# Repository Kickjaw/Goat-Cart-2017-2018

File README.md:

# Goat-Cart-2017-2018
Repository for all code, circuit diagrams, datasheets, and other useful documents.

stuff

jared was here

jade did stuff to sabertooth

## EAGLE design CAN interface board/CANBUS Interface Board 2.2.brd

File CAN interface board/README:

VERSION2 from 2017-18 MQP Team, as of March 2018 this is the CAN board.

Read more at the 2017-18 MQP report section 3.1

The second version of the board fixed the errors found in the first PCB and further optimized the layout.
The CAN transceiver was replaced with a SN65HVD23x 3.3-V CAN Bus Transceiver. [16]

The second board has:
•	Voltage regulation
•	+12V to +5V 
•	+5V to +3V3 (Teensy)
•	2 Power LEDs
•	+5V 
•	+3V3 
•	3 Programmable LEDs
•	2 differential CAN ports (link together via daisy chain method)
•	2 SPI Ports
•	2 Serial Ports
•	2 I2C Ports
•	16 Digital Pins
•	10 Analog Pins
•	5 PWM Pins

The primary goal of this design was to have many different methods of communication from the Teensy so that it could communicate to any type of sensor that a future team might use on the Goat Cart. Another reason for having numerous pins available was to allow a single Teensy to be used to control multiple subsystems. The only problem with the design was that, since the pins are software programmable, using a pin for a certain function could limit the availability of its other functions. An example of this is using pin 10 for PWM prevents its use as one of the SPI channels. The list of connector pinouts can be seen in Table 4. Figures 13 show the circuit and PCB of the second version of the CAN interface board.

Table 5: Pinouts of the Teensy used in the CAN Interface Board
Pinouts for the CAN Interface Board
1.	GND 
2.	3.3V
3.	CAN L0
4.	CAN H0
5.	CAN L
6.	CAN H
7.	Pin 32 - D/A/RX4/CS1
8.	Pin 31 -  D/A/TX4/SCK1
9.	Pin 12 - D/MISO0
10.	Pin 11 -  D/MISI0
11.	Pin 10 - D/PWM/TX2/CS0
12.	Pin 13 - D/SCK0	13.	Pin 33 - D/A/TX5
14.	Pin 34 - D/A/RX5
15.	Pin 37 - D/A/PWM/SCL1
16.	Pin 38 - D/A/PWM/SDA1
17.	Pin 18 - D/A/SDA0
18.	Pin 19 - D/A/SCL0
19.	Pin 22 - D/A/PWM
20.	Pin 23 - D/A/PWM
21.	Pin 1 -  D/TX1/MISO1
22.	Pin 0 - D/RX1/MOSI1
23.	3.3V
24.	GND

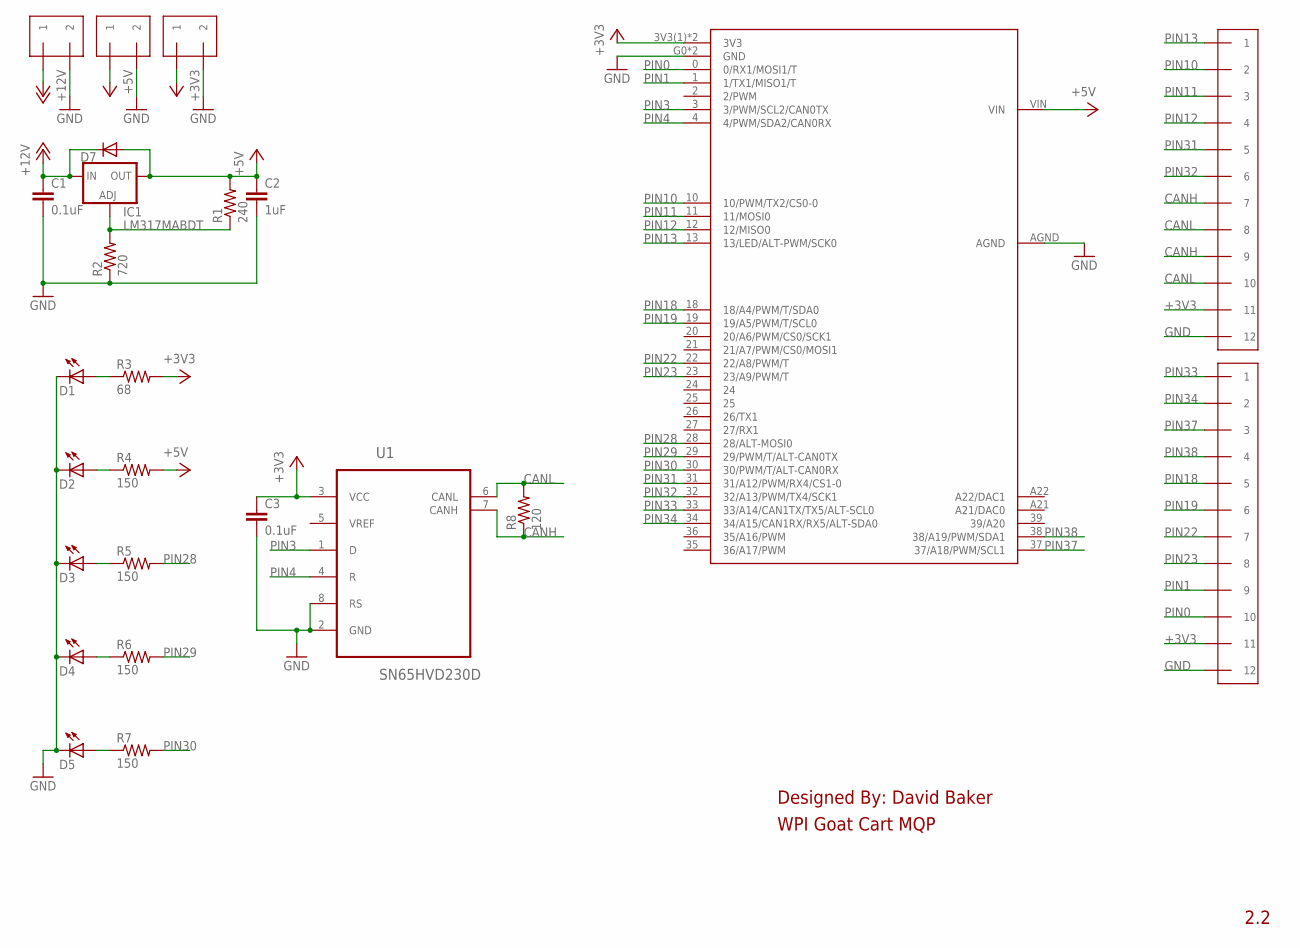
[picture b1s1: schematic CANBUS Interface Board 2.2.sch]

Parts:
C1, C3: 0.1uF; C0603
C2: 1uF; C0603
D1, D2, D3, D4, D5: LEDSML0603; SML0603
D7: DIODE-DO-214AC; DO-214AC
IC1: LM317MABDT; DPACK
J1, J2: 1984617X12; 12POSTERMBLOCK
J3, J4, J5: 1984617; 2POSTERMBLOCK
R1: 240; R0603
R2: 720; R0603
R3: 68; R0603
R4, R5, R6, R7: 150; R0603
R8: 120; R0603
U1: SN65HVD230D; SOIC127P600X175-8N
U2: TEENSY3_6--ALLPINS; T36

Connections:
+3V3: C3.1, J1.11, J2.11, J5.1, R3.2, U1.3 (VCC), U2.3V3(1) (3V3), U2.3V3(3) (3V3)
+5V: C2.1, D7.A, IC1.4 (OUT), J4.1, R1.2, R4.2, U2.VIN
+12V: C1.1, D7.C, IC1.3 (IN), J3.1
CANH: J1.7, J1.9, R8.1, U1.7 (CANH)
CANL: J1.8, J1.10, R8.2, U1.6 (CANL)
GND: C1.2, C2.2, C3.2, D1.C, D2.C, D3.C, D4.C, D5.C, J1.12, J2.12, J3.2, J4.2, J5.2, R2.1, U1.2 (GND), U1.8 (RS), U2.AGND, U2.G0 (GND), U2.G2 (GND)
unnamed: IC1.1 (ADJ), R1.1, R2.2
unnamed: D1.A, R3.1
unnamed: D2.A, R4.1
unnamed: D3.A, R5.1
unnamed: D4.A, R6.1
unnamed: D5.A, R7.1
PIN0: J2.10, U2.0 (0/RX1/MOSI1/T)
PIN1: J2.9, U2.1 (1/TX1/MISO1/T)
PIN3: U1.1 (D), U2.3 (3/PWM/SCL2/CAN0TX)
PIN4: U1.4 (R), U2.4 (4/PWM/SDA2/CAN0RX)
PIN10: J1.2, U2.10 (10/PWM/TX2/CS0-0)
PIN11: J1.3, U2.11 (11/MOSI0)
PIN12: J1.4, U2.12 (12/MISO0)
PIN13: J1.1, U2.13 (13/LED/ALT-PWM/SCK0)
PIN18: J2.5, U2.18 (18/A4/PWM/T/SDA0)
PIN19: J2.6, U2.19 (19/A5/PWM/T/SCL0)
PIN22: J2.7, U2.22 (22/A8/PWM/T)
PIN23: J2.8, U2.23 (23/A9/PWM/T)
PIN28: R5.2, U2.28 (28/ALT-MOSI0)
PIN29: R6.2, U2.29 (29/PWM/T/ALT-CAN0TX)
PIN30: R7.2, U2.30 (30/PWM/T/ALT-CAN0RX)
PIN31: J1.5, U2.31 (31/A12/PWM/RX4/CS1-0)
PIN32: J1.6, U2.32 (32/A13/PWM/TX4/SCK1)
PIN33: J2.1, U2.33 (33/A14/CAN1TX/TX5/ALT-SCL0)
PIN34: J2.2, U2.34 (34/A15/CAN1RX/RX5/ALT-SDA0)
PIN37: J2.3, U2.37 (37/A18/PWM/SCL1)
PIN38: J2.4, U2.38 (38/A19/PWM/SDA1)

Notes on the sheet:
Designed By: David Baker
WPI Goat Cart MQP
2.2

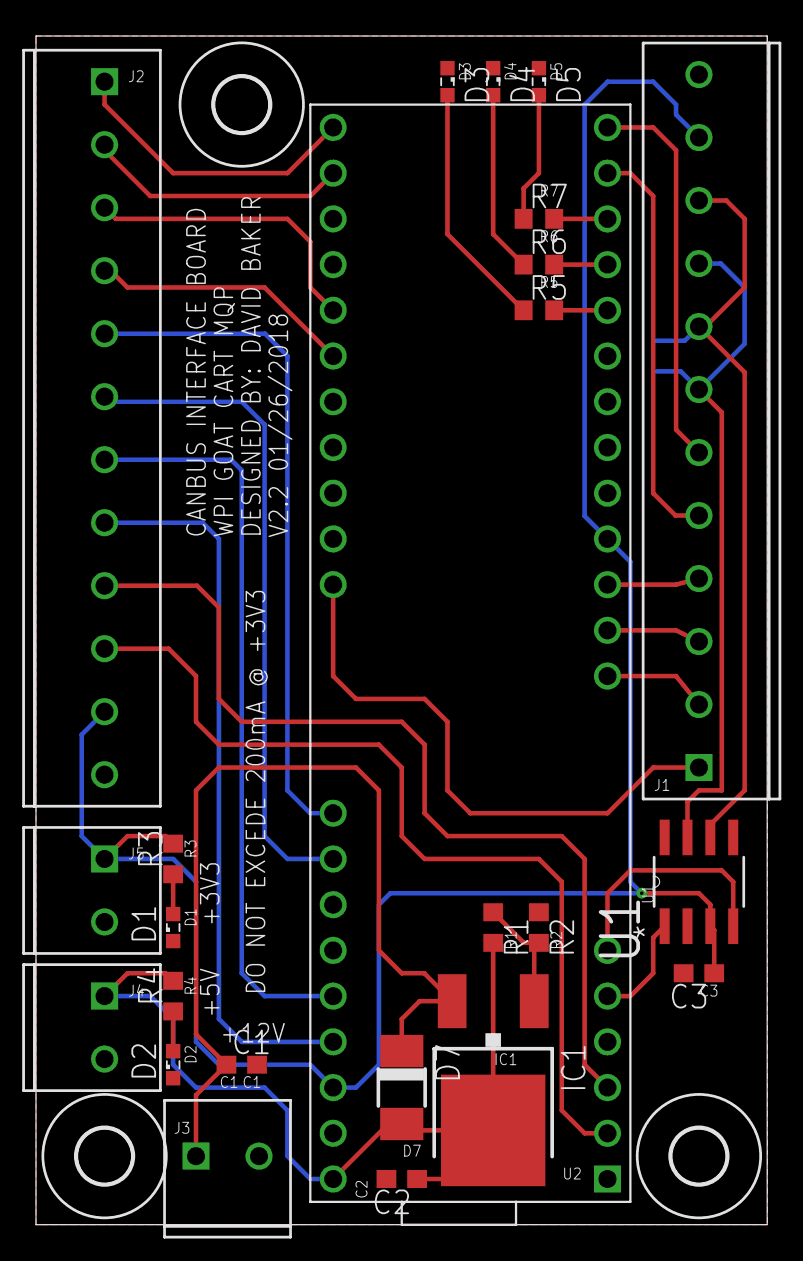
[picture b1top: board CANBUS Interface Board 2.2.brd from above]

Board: 2 copper layers, 40.6 x 66.0 mm, 28 parts (1 on the bottom side), 33 nets.

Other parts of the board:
U$1, U$2, U$3: 3,0

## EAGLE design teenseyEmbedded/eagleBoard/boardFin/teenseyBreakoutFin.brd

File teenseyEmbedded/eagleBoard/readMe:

This folder contains the Eagle files for the board and the files needed to have the PCB made.
In 2017 we have had the boards printed by PCBway.

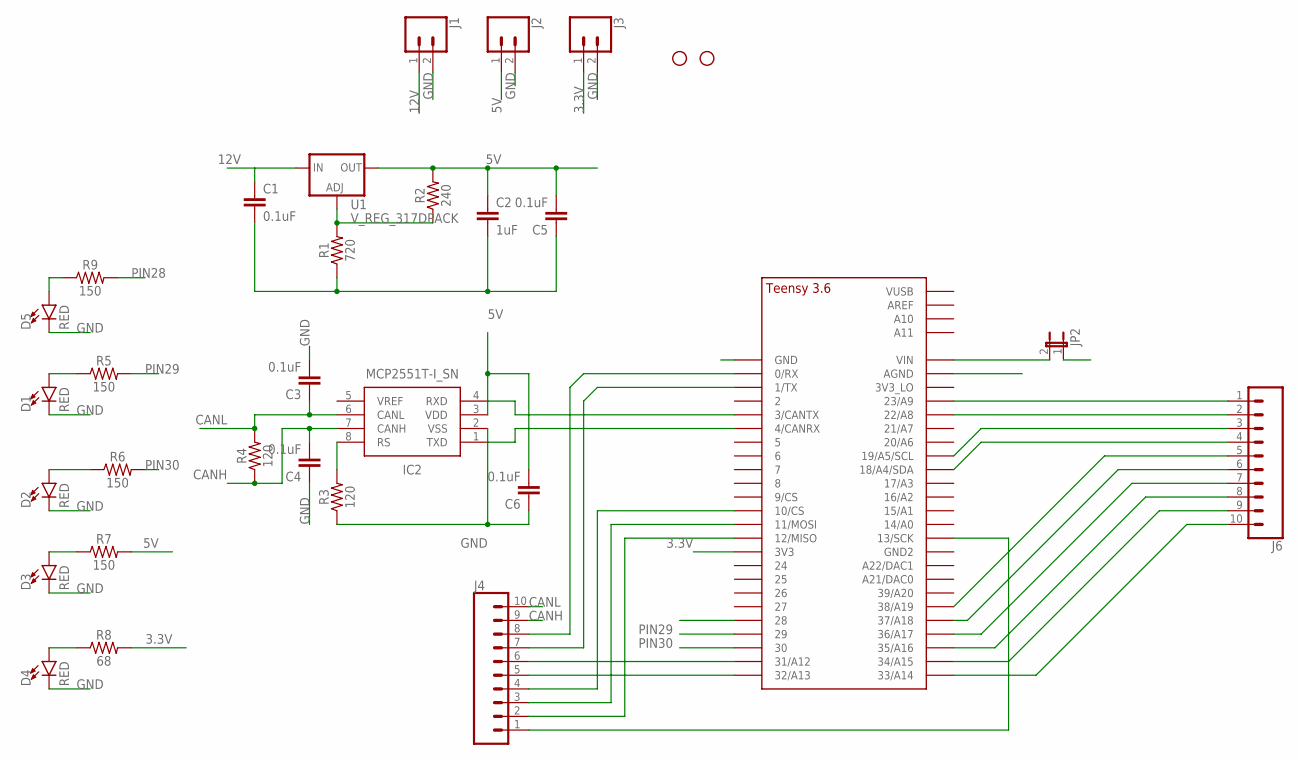
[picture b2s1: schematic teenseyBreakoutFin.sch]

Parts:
C1: 0.1uF; 0402
C2: 1uF; 0603
C3, C4, C5, C6: 0.1uF; 0603
D1, D2, D3, D4, D5: RED; LED-0603
H2: STAND-OFF
IC2: MCP2551T-I_SN; SOIC127P600X175-8N
J1, J2, J3: CONN_023.5MM_LOCK; SCREWTERMINAL-3.5MM-2_LOCK
J4, J6: CONN_10LOCK; 1X10_LOCK
JP2: JP1E; JP1
R1: 720; 0603
R2: 240; 0603
R3: 120; 0603
R4: 120; AXIAL-0.3
R5, R6, R7, R9: 150; 0603
R8: 68; 0603
SCREW_HOLE: STAND-OFF
U1: V_REG_317DPACK; V-REG_DPACK
U$1: TEENSY_3.5/3.6_BASIC

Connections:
3.3V: J3.1, R8.2, U$1.3V3
5V: C2.1, C5.2, C6.2, IC2.3 (VDD), J2.1, JP2.1, R2.2, R7.2, U1.4 (OUT)
12V: C1.1, J1.1, U1.3 (IN)
CANH: C4.2, IC2.7 (CANH), J4.9, R4.P$1 (1)
CANL: C3.1, IC2.6 (CANL), J4.10, R4.P$2 (2)
GND: C1.2, C2.2, C3.2, C4.1, C5.1, C6.1, D1.C, D2.C, D3.C, D4.C, D5.C, IC2.2 (VSS), J1.2, J2.2, J3.2, R1.1, R3.1, U$1.AGND, U$1.GND
unnamed: IC2.1 (TXD), U$1.4/CANRX
unnamed: J4.8, U$1.0/RX
unnamed: R1.2, R2.1, U1.1 (ADJ)
unnamed: J4.7, U$1.1/TX
unnamed: J4.6, U$1.31/A12
unnamed: J4.5, U$1.32/A13
unnamed: J4.4, U$1.10/CS
unnamed: IC2.4 (RXD), U$1.3/CANTX
unnamed: J4.1, U$1.13/SCK
unnamed: IC2.8 (RS), R3.2
unnamed: J4.3, U$1.11/MOSI
unnamed: J4.2, U$1.12/MISO
unnamed: J6.1, U$1.23/A9
unnamed: J6.2, U$1.22/A8
unnamed: J6.3, U$1.19/A5/SCL
unnamed: J6.4, U$1.18/A4/SDA
unnamed: J6.5, U$1.38/A19
unnamed: J6.6, U$1.37/A18
unnamed: J6.7, U$1.36/A17
unnamed: J6.8, U$1.35/A16
unnamed: J6.9, U$1.34/A15
unnamed: J6.10, U$1.33/A14
unnamed: D1.A, R5.1
unnamed: D5.A, R9.1
unnamed: D2.A, R6.1
unnamed: D3.A, R7.1
unnamed: D4.A, R8.1
PIN28: R9.2, U$1.28
PIN29: R5.2, U$1.29
PIN30: R6.2, U$1.30
VIN: JP2.2, U$1.VIN

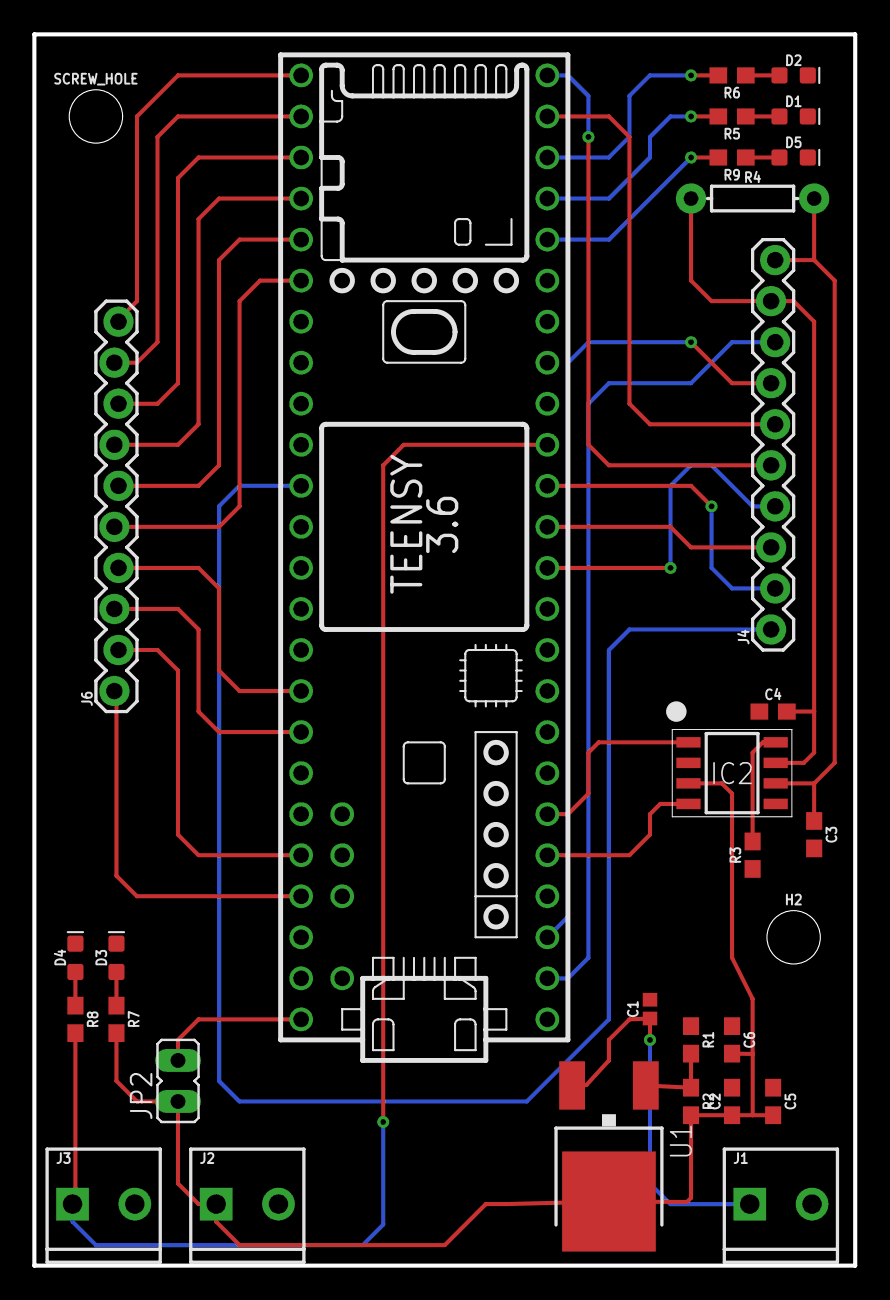
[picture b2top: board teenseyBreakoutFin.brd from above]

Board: 2 copper layers, 50.8 x 76.2 mm, 31 parts (0 on the bottom side), 37 nets.

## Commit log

2017-10-24 Set up folders
    set up folder system for organization
2017-10-24 Added current working braking code
2017-10-24 added more floders
2017-10-24 Create teenseyBoards
2017-10-26 added changes to readme
2017-10-26 created CANfile
2017-10-28 readme.txt CAN
    Description of CAN messages and how are they going to be used
2017-10-28 modiification
2017-10-29 added new braking code
    does not work yet
2017-10-31 Throttle and brake code is working as expected
    code is working, untested on the motors
2017-10-31 Moved files
2017-11-01 updated code codumentation
2017-11-01 fixed code
2017-11-02 modified the readme
    worte i did stuff
2017-11-02 jade updae steering stuff
2017-11-02 Update and rename test.txt to readMe
2017-11-02 jade fix
2017-11-03 changed code
2017-11-03 added golfcart.txtt
2017-11-04 code done need to do physical testing once brake motor is installed
2017-11-08 done
2017-11-08 Speedometer/Odometer V1.3
    Problems include:
    -Multiple sensor reads on signle pass
    -Multple sensor reads when magnet is fixed in front of sensor
2017-11-08 first draft working demo with LED
2017-11-09 Work Speedometer/Odometer
    -Works with 4 magnets (1 at each 45 degreee interval on wheel)
    -Accounts for debouncing
    -Accounts for when magnet is directly in front of sensor
    -Only accepts one read at a time (no double read on pass of magnet)
    -IN OTHER WORDS: WORDS FANTASTIC!
2017-11-10 Odometry, Throttle amd Breaking Demo Code
2017-11-10 nothing
2017-11-10 fullcart with steering
2017-11-10 Stuff
2017-11-10 raw control working
2018-03-16 CAN tests
2018-03-16 tests available
2018-03-19 cool tests
2018-03-20 addons to the test6
2018-03-20 changed starting server message

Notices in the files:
parts and their libraries:
SparkFun-Capacitors: Licensing: Creative Commons ShareAlike 4.0 International - https://creativecommons.org/licenses/by-sa/4.0
